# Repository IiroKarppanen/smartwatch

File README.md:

## Features
- nRF5340 SoC
- 240x240 LCD display
- Pulseoximetry
- GNSS
- Accelometer & Gyroscope
- Accurate RTC with backup battery

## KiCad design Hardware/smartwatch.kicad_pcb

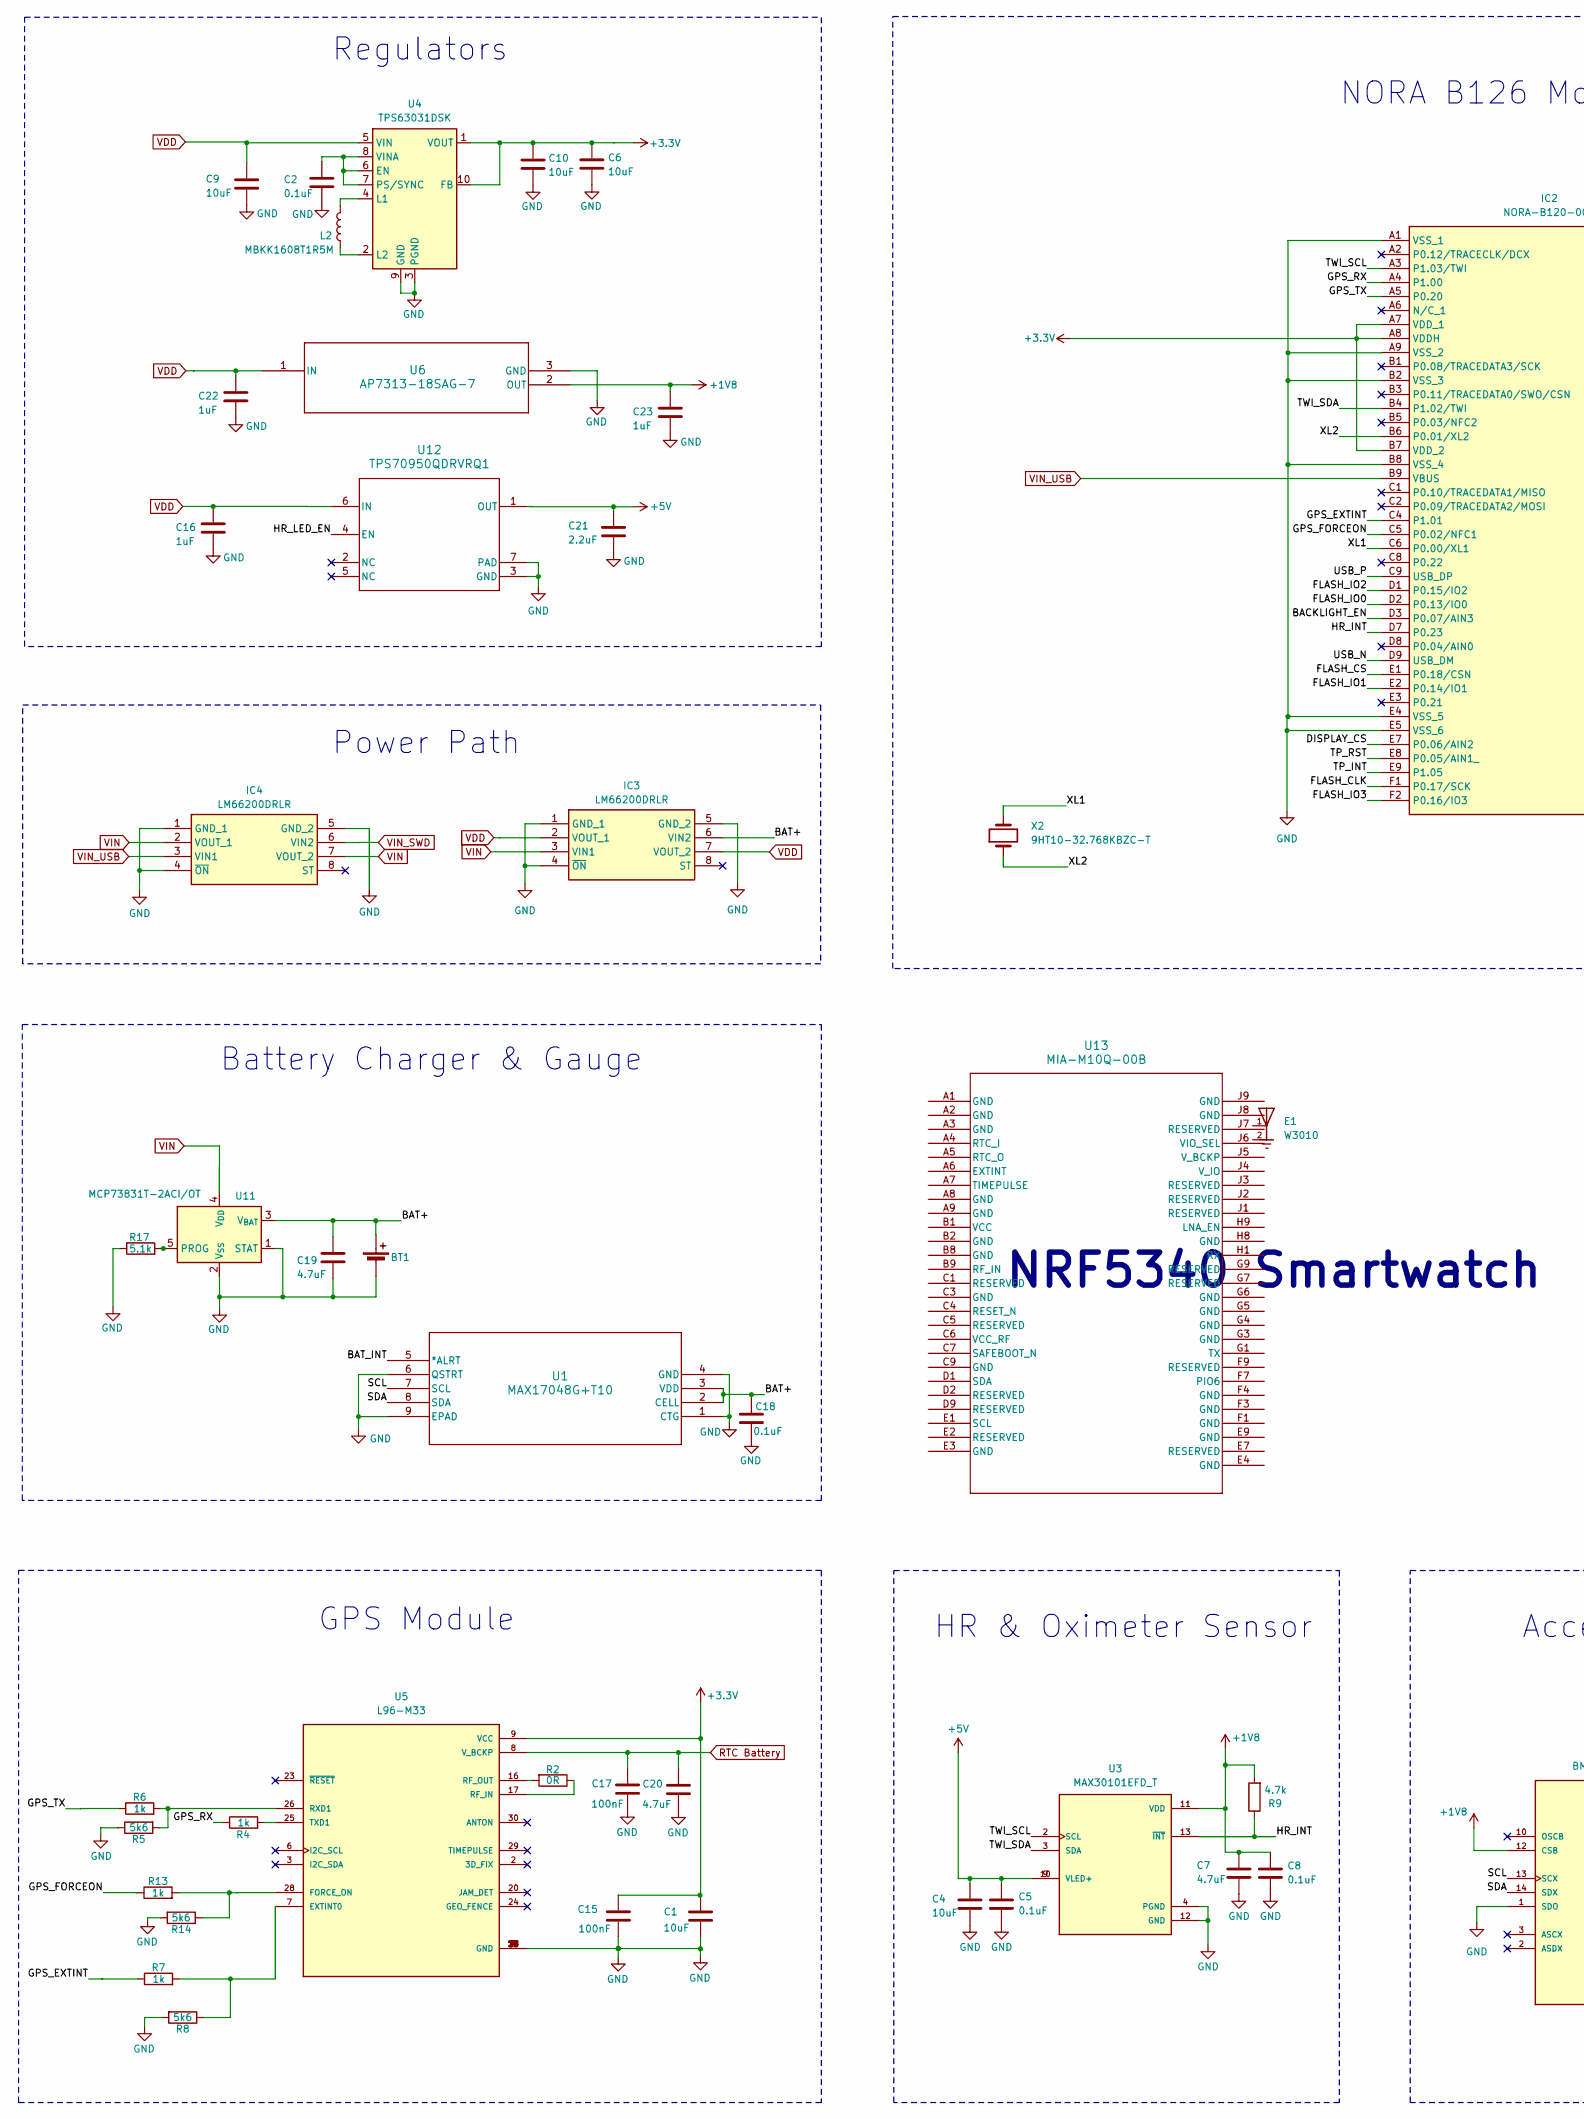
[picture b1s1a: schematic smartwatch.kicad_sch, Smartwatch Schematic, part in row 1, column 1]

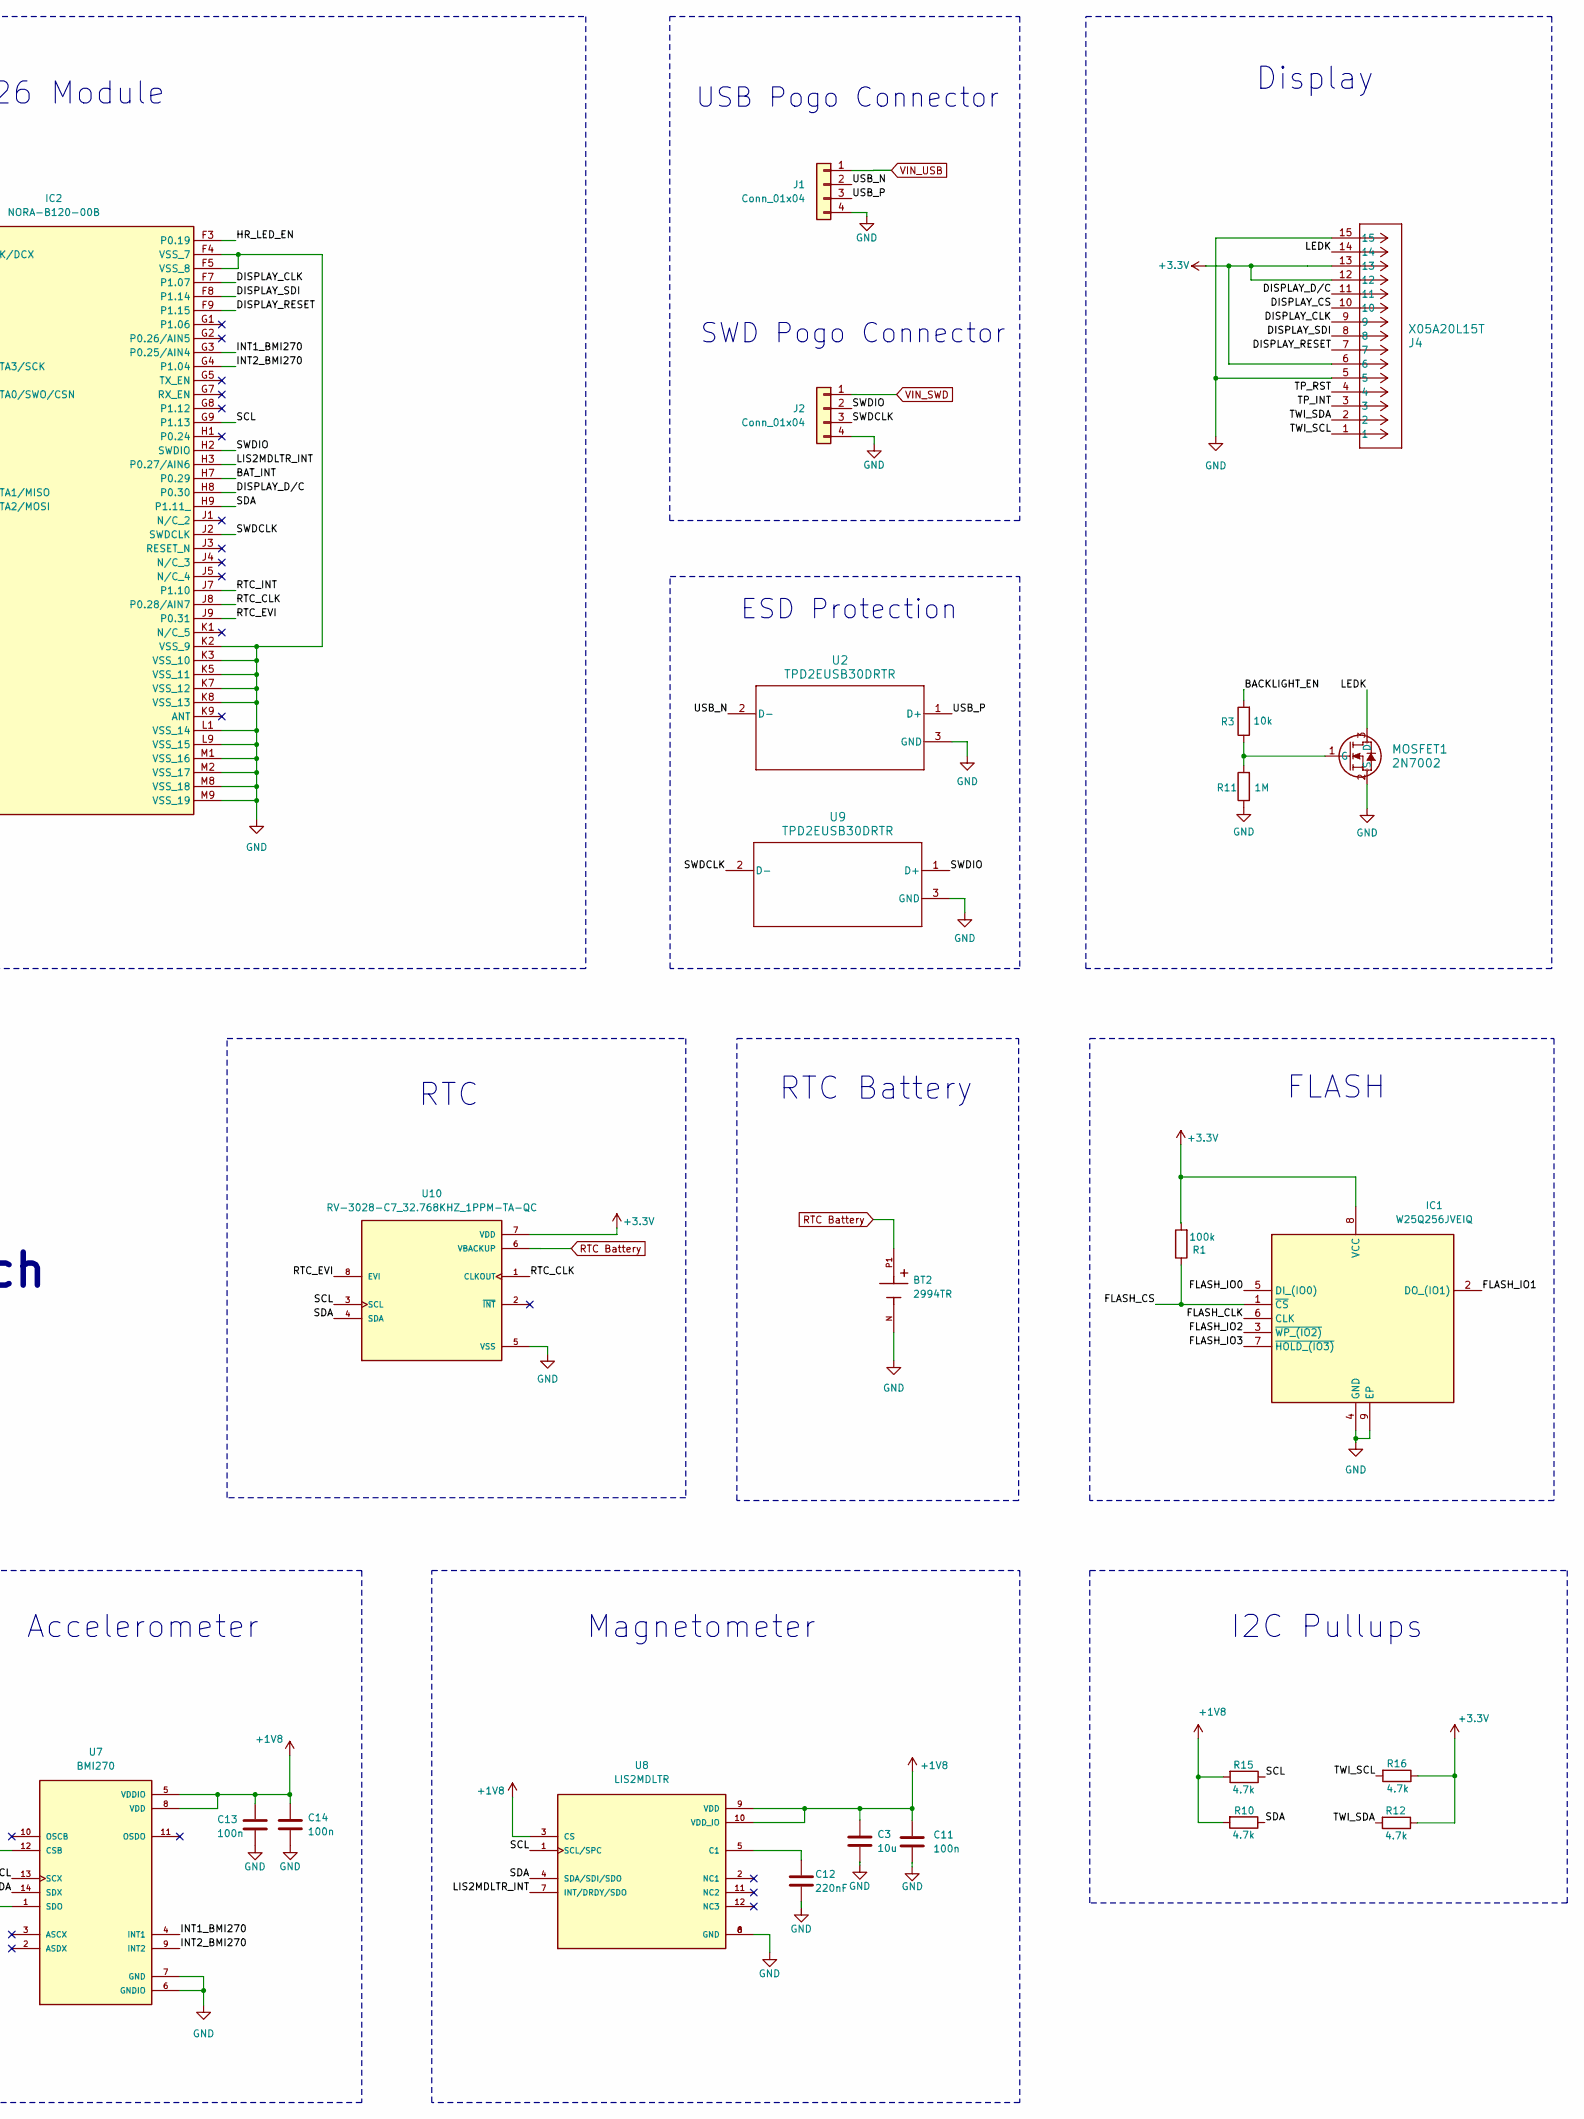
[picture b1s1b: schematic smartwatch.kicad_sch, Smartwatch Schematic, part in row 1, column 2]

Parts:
BT1: Battery_Cell; C_1812_4532Metric_Pad1.57x3.40mm_HandSolder
BT2: 2994TR; BAT_2994TR; PARTREV E
C1, C4, C6, C9, C10: 10uF; C_0402_1005Metric
C2, C5, C8: 0.1uF; C_0402_1005Metric
C3: 10u; C_0201_0603Metric
C7, C19, C20: 4.7uF; C_0402_1005Metric
C11, C13, C14: 100n; C_0201_0603Metric
C12: 220nF; C_0201_0603Metric
C15, C17: 100nF; C_0402_1005Metric
C16, C22, C23: 1uF; C_0402_1005Metric
C18: 0.1uF; C_0201_0603Metric
C21: 2.2uF; C_0402_1005Metric
E1: W3010; XCVR_W3010; PARTREV L192.C 2/16
IC1: W25Q256JVEIQ; SON127P800X600X80-9N-D; Mouser Part Number 454-W25N01GVZEIGTR
IC2: NORA-B120-00B; NORAB12000B; Mouser Part Number 377-NORA-B120-00B
IC3, IC4: LM66200DRLR; SOTFL50P160X60-8N; Mouser Part Number 595-LM66200DRLR
J1, J2: Conn_01x04; Pogo_Female_4Pin
J4: X05A20L15T; CONN_X05A20L15T_XKB
L2: MBKK1608T1R5M; L_0603_1608Metric
MOSFET1: 2N7002; SOT-23TO-236_318-08_ONS
R1: 100k; R_0402_1005Metric; MPN NRF52840-QIAA-R
R2: 0R; R_0402_1005Metric
R3: 10k; R_0402_1005Metric
R4, R6, R7, R13: 1k; R_0402_1005Metric
R5, R8, R14: 5k6; R_0402_1005Metric
R9: 4.7k; R_0402_1005Metric; MPN NRF52840-QIAA-R
R10, R12, R15, R16: 4.7k; R_0201_0603Metric; MPN NRF52840-QIAA-R
R11: 1M; R_0402_1005Metric
R17: 5.1k; R_0402_1005Metric
U1: MAX17048G+T10; 21-0168E_T822-3_MXM
U2, U9: TPD2EUSB30DRTR; DRT0003A
U3: MAX30101EFD_T; PARTREV 2
U4: TPS63031DSK; WSON-10-1EP_2.5x2.5mm_P0.5mm_EP1.2x2mm
U5: L96-M33; XCVR_L96-M33; DigiKey_Part_Number 2958-L96-M33TR-ND
U6: AP7313-18SAG-7; SOT-23_DIO
U7: BMI270; XDCR_BMI270
U8: LIS2MDLTR; PQFN50P200X200X70-12N; PARTREV Rev 5
U10: RV-3028-C7_32.768KHZ_1PPM-TA-QC; IC_RV-3028-C7_32.768KHZ_1PPM-TA-QC; PARTREV 1.3
U11: MCP73831T-2ACI/OT; SOT-23-5; MPN MCP73831-2-OT
U12: TPS70950QDRVRQ1; DRV0006A
U13: MIA-M10Q-00B; LGA_M10Q-00B_UBL
X2: 9HT10-32.768KBZC-T; Crystal_SMD_3215-2Pin_3.2x1.5mm

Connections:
+1V8: C3.1, C7.1, C8.1, C11.1, C13.1, C14.1, C23.1, R9.2, R10.2, R15.2, U3.11 (VDD), U6.2 (OUT), U7.5 (VDDIO), U7.8 (VDD), U7.12 (CSB), U8.3 (CS), U8.9 (VDD), U8.10 (VDD_IO)
+3.3V: C1.1, C6.1, C10.1, C15.1, IC1.8 (VCC), IC2.A7 (VDD_1), IC2.A8 (VDDH), IC2.B7 (VDD_2), J4.6, J4.12, J4.13, R1.2, R12.1, R16.1, U4.1 (VOUT), U4.10 (FB), U5.9 (VCC), U10.7 (VDD)
+5V: C4.1, C5.1, C21.1, U3.9 (VLED+), U3.10 (VLED+), U12.1 (OUT)
/BACKLIGHT_EN: IC2.D3 (P0.07/AIN3), R3.2
/BAT+: BT1.1 (+), C18.1, C19.1, IC3.6 (VIN2), U1.2 (CELL), U1.3 (VDD), U11.3 (V_{BAT})
/BAT_INT: IC2.H7 (P0.29), U1.5 (*ALRT)
/DISPLAY_CLK: IC2.F7 (P1.07), J4.9
/DISPLAY_CS: IC2.E7 (P0.06/AIN2), J4.10
/DISPLAY_D/C: IC2.H8 (P0.30), J4.11
/DISPLAY_RESET: IC2.F9 (P1.15), J4.7
/DISPLAY_SDI: IC2.F8 (P1.14), J4.8
/FLASH_CLK: IC1.6 (CLK), IC2.F1 (P0.17/SCK)
/FLASH_CS: IC1.1 (~CS), IC2.E1 (P0.18/CSN), R1.1
/FLASH_IO0: IC1.5 (DI_(IO0)), IC2.D2 (P0.13/IO0)
/FLASH_IO1: IC1.2 (DO_(IO1)), IC2.E2 (P0.14/IO1)
/FLASH_IO2: IC1.3 (~WP_(IO2)), IC2.D1 (P0.15/IO2)
/FLASH_IO3: IC1.7 (~HOLD_(IO3)), IC2.F2 (P0.16/IO3)
/GPS_EXTINT: IC2.C4 (P1.01), R7.1
/GPS_FORCEON: IC2.C5 (P0.02/NFC1), R13.1
/GPS_RX: IC2.A4 (P1.00), R4.1
/GPS_TX: IC2.A5 (P0.20), R6.1
/HR_INT: IC2.D7 (P0.23), R9.1, U3.13 (~INT)
/HR_LED_EN: IC2.F3 (P0.19), U12.4 (EN)
/INT1_BMI270: IC2.G3 (P0.25/AIN4), U7.4 (INT1)
/INT2_BMI270: IC2.G4 (P1.04), U7.9 (INT2)
/LEDK: J4.14, MOSFET1.3 (D)
/LIS2MDLTR_INT: IC2.H3 (P0.27/AIN6), U8.7 (INT/DRDY/SDO)
/RTC_CLK: IC2.J8 (P0.28/AIN7), U10.1 (CLKOUT)
/RTC_EVI: IC2.J9 (P0.31), U10.8 (EVI)
/RTC_INT: IC2.J7 (P1.10)
/SCL: IC2.G9 (P1.13), R15.1, U1.7 (SCL), U7.13 (SCX), U8.1 (SCL/SPC), U10.3 (SCL)
/SDA: IC2.H9 (P1.11_), R10.1, U1.8 (SDA), U7.14 (SDX), U8.4 (SDA/SDI/SDO), U10.4 (SDA)
/SWDCLK: IC2.J2 (SWDCLK), J2.3, U9.2 (D-)
/SWDIO: IC2.H2 (SWDIO), J2.2, U9.1 (D+)
/TP_INT: IC2.E9 (P1.05), J4.3
/TP_RST: IC2.E8 (P0.05/AIN1_), J4.4
/TWI_SCL: IC2.A3 (P1.03/TWI), J4.1, R16.2, U3.2 (SCL)
/TWI_SDA: IC2.B4 (P1.02/TWI), J4.2, R12.2, U3.3 (SDA)
/USB_N: IC2.D9 (USB_DM), J1.2, U2.2 (D-)
/USB_P: IC2.C9 (USB_DP), J1.3, U2.1 (D+)
/XL1: IC2.C6 (P0.00/XL1), X2.2
/XL2: IC2.B6 (P0.01/XL2), X2.1
GND: BT1.2 (-), BT2.N, C1.2, C2.2, C3.2, C4.2, C5.2, C6.2, C7.2, C8.2, C9.2, C10.2, C11.2, C12.2, C13.2, C14.2, C15.2, C16.2, C17.2, C18.2, C19.2, C20.2, C21.2, C22.2, C23.2, IC1.4 (GND), IC1.9 (EP), IC2.A1 (VSS_1), IC2.A9 (VSS_2), IC2.B2 (VSS_3), IC2.B8 (VSS_4), IC2.E4 (VSS_5), IC2.E5 (VSS_6), IC2.F4 (VSS_7), IC2.F5 (VSS_8), IC2.K2 (VSS_9), IC2.K3 (VSS_10), IC2.K5 (VSS_11), IC2.K7 (VSS_12), IC2.K8 (VSS_13), IC2.L1 (VSS_14), IC2.L9 (VSS_15), IC2.M1 (VSS_16), IC2.M2 (VSS_17), IC2.M8 (VSS_18), IC2.M9 (VSS_19), IC3.1 (GND_1), IC3.4 (~ON), IC3.5 (GND_2), IC4.1 (GND_1), IC4.4 (~ON), IC4.5 (GND_2), J1.4, J2.4, J4.5, J4.15, MOSFET1.2 (S), R5.1, R8.2, R11.1, R14.2, R17.1, U1.1 (CTG), U1.4 (GND), U1.6 (QSTRT), U1.9 (EPAD), U2.3 (GND), U3.4 (PGND), U3.12 (GND), U4.3 (PGND), U4.9 (GND), U4.11 (PGND), U5.4 (GND), U5.5 (GND), U5.10 (GND), U5.11 (GND), U5.12 (GND), U5.13 (GND), U5.14 (GND), U5.15 (GND), U5.18 (GND), U5.19 (GND), U5.21 (GND), U5.22 (GND), U5.27 (GND), U5.31 (GND), U6.3 (GND), U7.1 (SDO), U7.6 (GNDIO), U7.7 (GND), U8.6 (GND), U8.8 (GND), U9.3 (GND), U10.5 (VSS), U11.1 (STAT), U11.2 (V_{SS}), U12.3 (GND), U12.7 (PAD)
unnamed: MOSFET1.1 (G), R3.1, R11.2
unnamed: C2.1, U4.6 (EN), U4.7 (PS/SYNC), U4.8 (VINA)
unnamed: L2.2, U4.4 (L1)
unnamed: L2.1, U4.2 (L2)
unnamed: R7.2, R8.1, U5.7 (EXTINT0)
unnamed: R13.2, R14.1, U5.28 (FORCE_ON)
unnamed: R2.1, U5.17 (RF_IN)
unnamed: R2.2, U5.16 (RF_OUT)
unnamed: R5.2, R6.2, U5.26 (RXD1)
unnamed: R4.2, U5.25 (TXD1)
unnamed: C12.1, U8.5 (C1)
unnamed: R17.2, U11.5 (PROG)
RTC Battery: BT2.P1, C17.1, C20.1, U5.8 (V_BCKP), U10.6 (VBACKUP)
VDD: C9.1, C16.1, C22.1, IC3.2 (VOUT_1), IC3.7 (VOUT_2), U4.5 (VIN), U6.1 (IN), U12.6 (IN)
VIN: IC3.3 (VIN1), IC4.2 (VOUT_1), IC4.7 (VOUT_2), U11.4 (V_{DD})
VIN_SWD: IC4.6 (VIN2), J2.1
VIN_USB: IC2.B9 (VBUS), IC4.3 (VIN1), J1.1

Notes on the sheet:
NORA B126 Module
NRF5340 Smartwatch
HR & Oximeter Sensor
Magnetometer
GPS Module
I2C Pullups
SWD Pogo Connector
RTC Battery
Battery Charger & Gauge
Display
Accelerometer
USB Pogo Connector
ESD Protection
FLASH
Power Path
RTC
Regulators

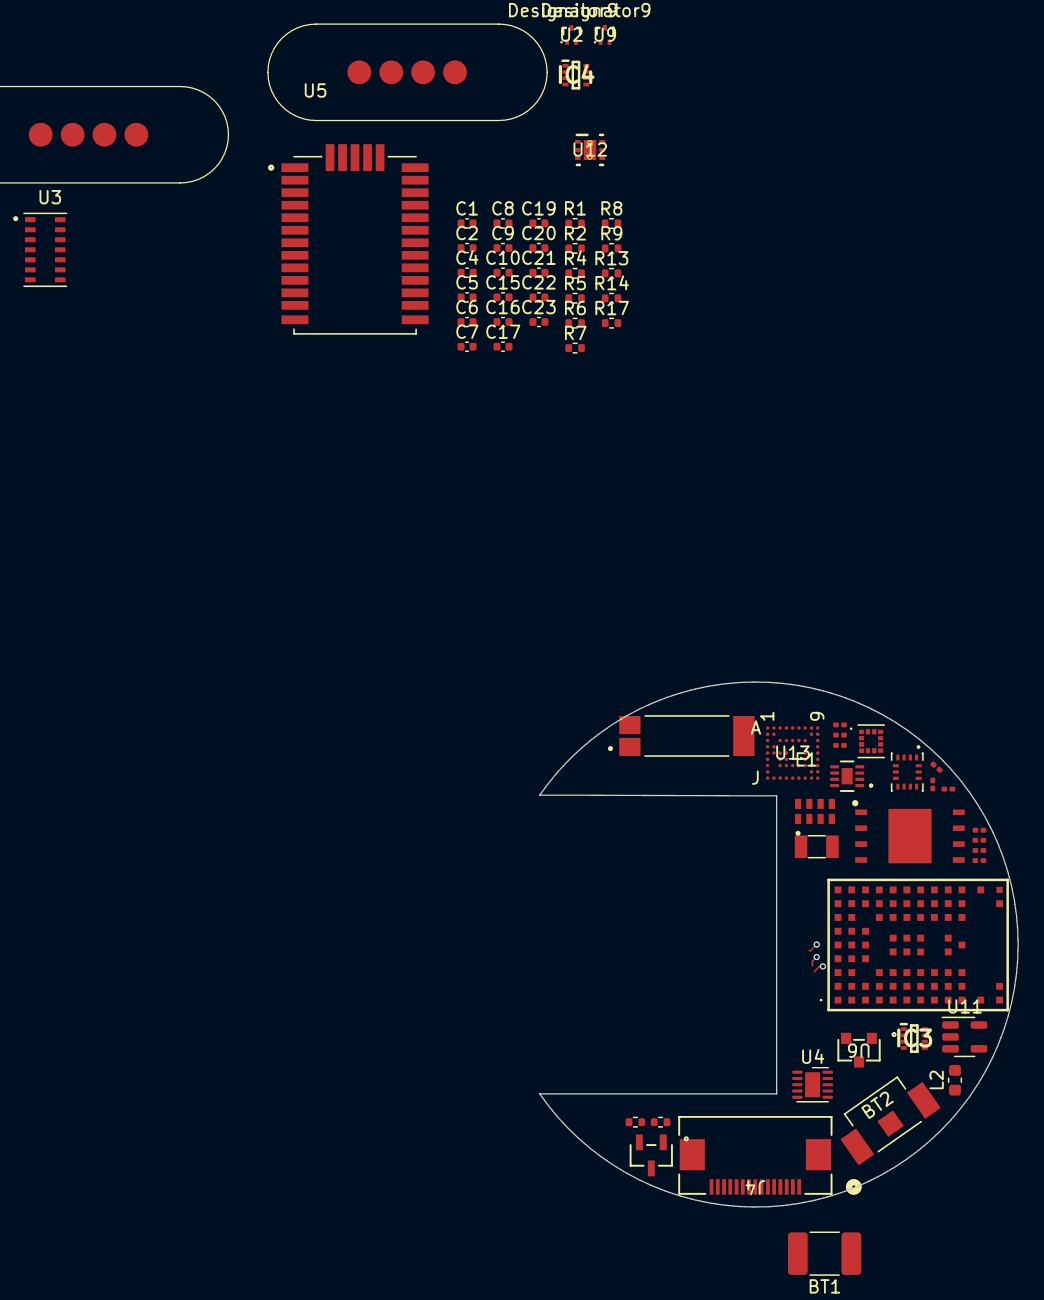
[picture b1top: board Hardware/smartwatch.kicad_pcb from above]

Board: 4 copper layers, 38.2 x 41.9 mm, 66 parts (0 on the bottom side), 59 nets.

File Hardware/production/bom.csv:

Designator,Footprint,Quantity,Value,LCSC Part #
BT1,1812,1,Battery_Cell,
BT2,BAT_2994TR,1,2994TR,
"C1, C10, C4, C6, C9",0402,5,10uF,
"C11, C13, C14",0402,3,100n,
C12,0402,1,220nF,
"C15, C17",0402,2,100nF,
"C16, C22, C23",0402,3,1uF,
"C18, C2, C5, C8",0402,4,0.1uF,
"C19, C20, C7",0402,3,4.7uF,
C21,0402,1,2.2uF,
C3,0402,1,10u,
IC1,SON127P800X600X80-9N-D,1,W25Q256JVEIQ,
IC2,NORAB12000B,1,NORA-B120-00B,
"IC3, IC4",SOTFL50P160X60-8N,2,LM66200DRLR,
"J1, J2",Pogo_Female_4Pin,2,Conn_01x04,
J4,CONN_X05A20L15T_XKB,1,X05A20L15T,
L2,0603,1,MBKK1608T1R5M,
MOSFET1,SOT-23TO-236_318-08_ONS,1,2N7002,
R1,0402,1,100k,NRF52840-QIAA-R
"R10, R12, R15, R16, R9",0402,5,4.7k,NRF52840-QIAA-R
R11,0402,1,1M,
"R13, R4, R6, R7",0402,4,1k,
"R14, R5, R8",0402,3,5k6,
R17,0402,1,5.1k,
R18,0805,1,470,
R2,0402,1,0R,
R3,0402,1,10k,
U1,21-0168E_T822-3_MXM,1,MAX17048G+T10,
U10,IC_RV-3028-C7_32.768KHZ_1PPM-TA-QC,1,RV-3028-C7_32.768KHZ_1PPM-TA-QC,
U11,SOT-23-5,1,MCP73831T-2ACI/OT,MCP73831-2-OT
U12,DRV0006A,1,TPS70950QDRVRQ1,
"U2, U9",DRT0003A,2,TPD2EUSB30DRTR,
U3,MAX30101EFD_T,1,MAX30101EFD_T,
U4,WSON-10-1EP_2.5x2.5mm_P0.5mm_EP1.2x2mm,1,TPS63031DSK,
U5,XCVR_L96-M33,1,L96-M33,
U6,SOT-23_DIO,1,AP7313-18SAG-7,
U7,XDCR_BMI270,1,BMI270,
U8,PQFN50P200X200X70-12N,1,LIS2MDLTR,
X2,Crystal_SMD_3215-2Pin_3.2x1.5mm,1,9HT10-32.768KBZC-T,

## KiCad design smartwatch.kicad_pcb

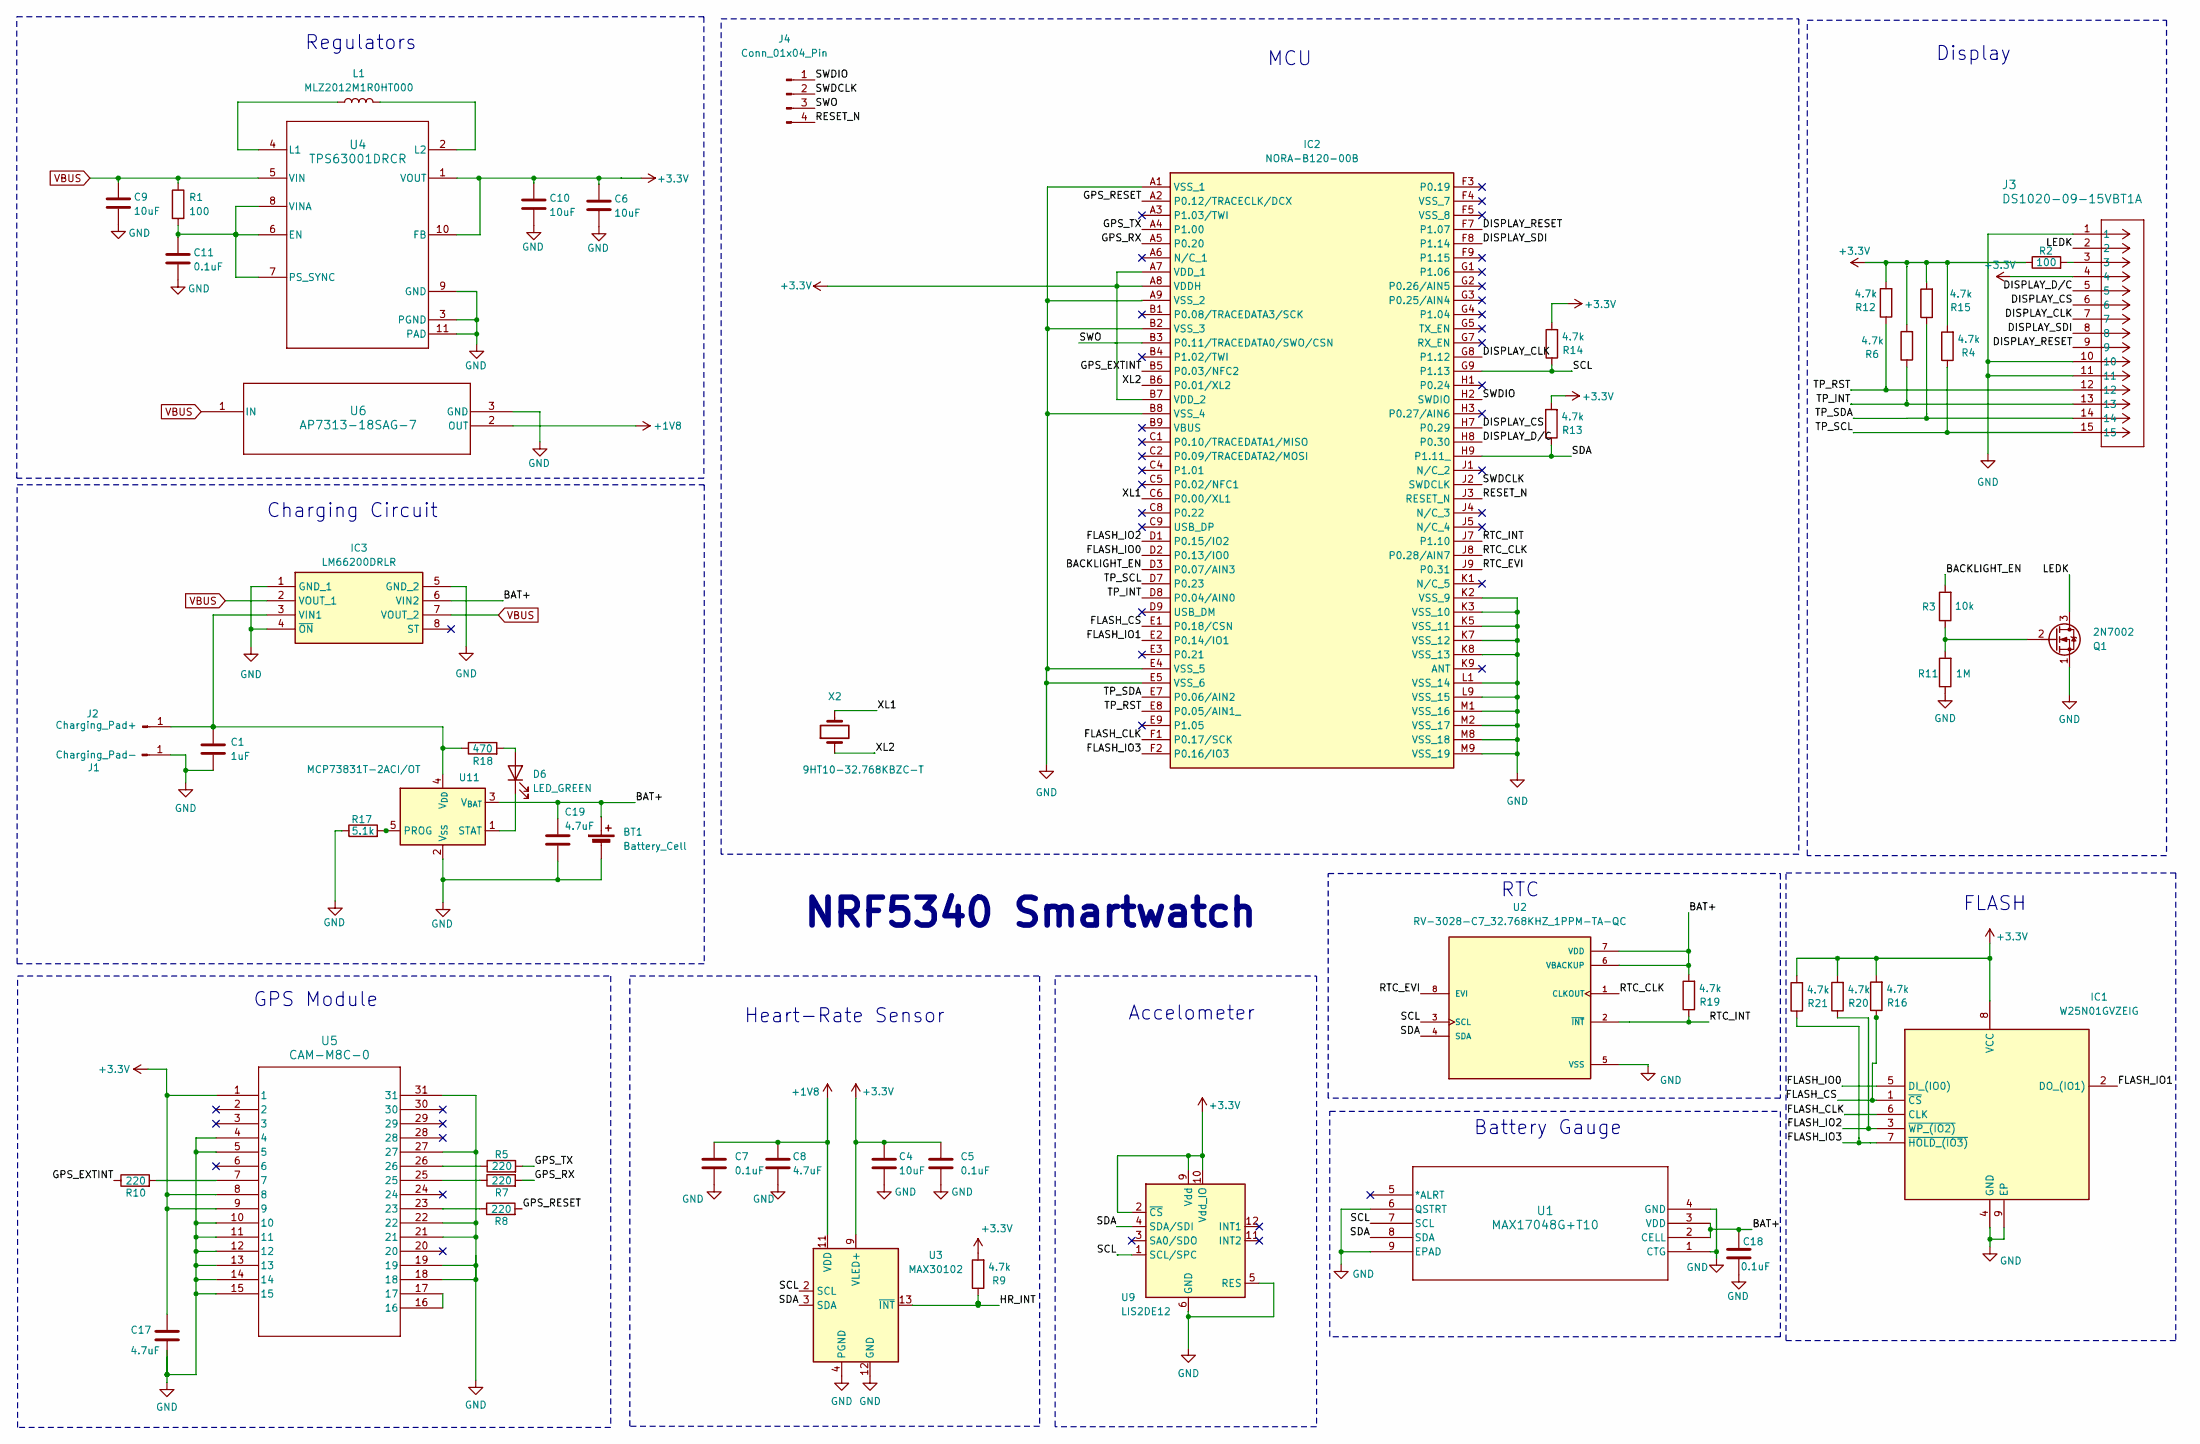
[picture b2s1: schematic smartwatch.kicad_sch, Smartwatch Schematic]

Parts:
BT1: Battery_Cell; C_1812_4532Metric
C1: 1uF; C_0402_1005Metric
C4, C6, C9, C10: 10uF; C_0402_1005Metric
C5, C7, C11, C18: 0.1uF; C_0402_1005Metric
C8, C17, C19: 4.7uF; C_0402_1005Metric
D6: LED_GREEN; LED_0402_1005Metric
IC1: W25N01GVZEIG; SON127P800X600X80-9N-D; Mouser Part Number 454-W25N01GVZEIGTR
IC2: NORA-B120-00B; NORAB12000B; Mouser Part Number 377-NORA-B120-00B
IC3: LM66200DRLR; SOTFL50P160X60-8N; Mouser Part Number 595-LM66200DRLR
J1: Charging_Pad-; power_pad_4mm
J2: Charging_Pad+; power_pad_4mm
J3: DS1020-09-15VBT1A; FPC-SMD_P0.50-15P_LSXJ-H2.0-15P
J4: Conn_01x04_Pin; PinHeader_1x04_P2.54mm_Vertical
L1: MLZ2012M1R0HT000; L_0805_2012Metric
Q1: 2N7002; SOT-23-3
R1: 100; R_0402_1005Metric
R2: 100; R_0603_1608Metric
R3: 10k; R_0603_1608Metric
R4, R6, R9, R12, R15, R16, R19, R20, R21: 4.7k; R_0402_1005Metric; MPN NRF52840-QIAA-R
R5, R7, R8, R10: 220; R_0402_1005Metric
R11: 1M; R_0603_1608Metric
R13, R14: 4.7k; R_0603_1608Metric; MPN NRF52840-QIAA-R
R17: 5.1k; R_0402_1005Metric
R18: 470; R_0402_1005Metric
U1: MAX17048G+T10; 21-0168E_T822-3_MXM
U2: RV-3028-C7_32.768KHZ_1PPM-TA-QC; IC_RV-3028-C7_32.768KHZ_1PPM-TA-QC; PARTREV 1.3
U3: MAX30102; Maxim_OLGA-14_3.3x5.6mm_P0.8mm
U4: TPS63001DRCR; DRC0010J
U5: CAM-M8C-0; QFN_M8C-0_UBL
U6: AP7313-18SAG-7; SOT-23_DIO
U9: LIS2DE12; LGA-12_2x2mm_P0.5mm; MPN LIS2DE12
U11: MCP73831T-2ACI/OT; SOT-23-5; MPN MCP73831-2-OT
X2: 9HT10-32.768KBZC-T; Crystal_SMD_3215-2Pin_3.2x1.5mm

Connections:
+1V8: C7.1, C8.1, U3.11 (VDD), U6.2 (OUT)
+3.3V: C4.1, C5.1, C6.1, C10.1, C17.1, IC1.8 (VCC), IC2.A7 (VDD_1), IC2.A8 (VDDH), IC2.B7 (VDD_2), J3.4, R2.1, R4.2, R6.2, R9.2, R12.2, R13.2, R14.2, R15.2, R16.2, R20.2, R21.2, U3.9 (VLED+), U3.10 (VLED+), U4.1 (VOUT), U4.10 (FB), U5.1, U5.8, U5.9, U9.2 (~CS), U9.9 (Vdd), U9.10 (Vdd_IO)
/BACKLIGHT_EN: IC2.D3 (P0.07/AIN3), R3.2
/BAT+: BT1.1 (+), C18.1, C19.1, IC3.6 (VIN2), R19.2, U1.2 (CELL), U1.3 (VDD), U2.6 (VBACKUP), U2.7 (VDD), U11.3 (V_{BAT})
/DISPLAY_CLK: IC2.G8 (P1.12), J3.7
/DISPLAY_CS: IC2.H7 (P0.29), J3.6
/DISPLAY_D/C: IC2.H8 (P0.30), J3.5
/DISPLAY_RESET: IC2.F7 (P1.07), J3.9
/DISPLAY_SDI: IC2.F8 (P1.14), J3.8
/FLASH_CLK: IC1.6 (CLK), IC2.F1 (P0.17/SCK)
/FLASH_CS: IC1.1 (~CS), IC2.E1 (P0.18/CSN), R16.1
/FLASH_IO0: IC1.5 (DI_(IO0)), IC2.D2 (P0.13/IO0)
/FLASH_IO1: IC1.2 (DO_(IO1)), IC2.E2 (P0.14/IO1)
/FLASH_IO2: IC1.3 (~WP_(IO2)), IC2.D1 (P0.15/IO2), R20.1
/FLASH_IO3: IC1.7 (~HOLD_(IO3)), IC2.F2 (P0.16/IO3), R21.1
/GPS_EXTINT: IC2.B5 (P0.03/NFC2), R10.1
/GPS_RESET: IC2.A2 (P0.12/TRACECLK/DCX), R8.2
/GPS_RX: IC2.A5 (P0.20), R7.2
/GPS_TX: IC2.A4 (P1.00), R5.2
/HR_INT: R9.1, U3.13 (~INT)
/LEDK: J3.2, Q1.3 (D)
/RESET_N: IC2.J3 (RESET_N), J4.4
/RTC_CLK: IC2.J8 (P0.28/AIN7), U2.1 (CLKOUT)
/RTC_EVI: IC2.J9 (P0.31), U2.8 (EVI)
/RTC_INT: IC2.J7 (P1.10), R19.1, U2.2 (~INT)
/SCL: IC2.G9 (P1.13), R14.1, U1.7 (SCL), U2.3 (SCL), U3.2 (SCL), U9.1 (SCL/SPC)
/SDA: IC2.H9 (P1.11_), R13.1, U1.8 (SDA), U2.4 (SDA), U3.3 (SDA), U9.4 (SDA/SDI)
/SWDCLK: IC2.J2 (SWDCLK), J4.2
/SWDIO: IC2.H2 (SWDIO), J4.1
/SWO: IC2.B3 (P0.11/TRACEDATA0/SWO/CSN), J4.3
/TP_INT: IC2.D8 (P0.04/AIN0), J3.13, R6.1
/TP_RST: IC2.E8 (P0.05/AIN1_), J3.12, R12.1
/TP_SCL: IC2.D7 (P0.23), J3.15, R4.1
/TP_SDA: IC2.E7 (P0.06/AIN2), J3.14, R15.1
/XL1: IC2.C6 (P0.00/XL1), X2.2
/XL2: IC2.B6 (P0.01/XL2), X2.1
GND: BT1.2 (-), C1.2, C4.2, C5.2, C6.2, C7.2, C8.2, C9.2, C10.2, C11.2, C17.2, C18.2, C19.2, IC1.4 (GND), IC1.9 (EP), IC2.A1 (VSS_1), IC2.A9 (VSS_2), IC2.B2 (VSS_3), IC2.B8 (VSS_4), IC2.E4 (VSS_5), IC2.E5 (VSS_6), IC2.K2 (VSS_9), IC2.K3 (VSS_10), IC2.K5 (VSS_11), IC2.K7 (VSS_12), IC2.K8 (VSS_13), IC2.L1 (VSS_14), IC2.L9 (VSS_15), IC2.M1 (VSS_16), IC2.M2 (VSS_17), IC2.M8 (VSS_18), IC2.M9 (VSS_19), IC3.1 (GND_1), IC3.4 (~ON), IC3.5 (GND_2), J1.1, J3.1, J3.10, J3.11, Q1.1 (S), R11.1, R17.1, U1.1 (CTG), U1.4 (GND), U1.6 (QSTRT), U1.9 (EPAD), U2.5 (VSS), U3.4 (PGND), U3.12 (GND), U4.3 (PGND), U4.9 (GND), U4.11 (PAD), U4.V, U5.4, U5.5, U5.10, U5.11, U5.12, U5.13, U5.14, U5.15, U5.18, U5.19, U5.21, U5.22, U5.27, U5.31, U6.3 (GND), U9.5 (RES), U9.6 (GND), U9.7 (GND), U9.8 (GND), U11.2 (V_{SS})
unnamed: D6.2 (A), R18.2
unnamed: D6.1 (K), U11.1 (STAT)
unnamed: C1.1, IC3.3 (VIN1), J2.1, R18.1, U11.4 (V_{DD})
unnamed: J3.3, R2.2
unnamed: Q1.2 (G), R3.1, R11.2
unnamed: R5.1, U5.26
unnamed: R7.1, U5.25
unnamed: R8.1, U5.23
unnamed: R10.2, U5.7
unnamed: C11.1, R1.2, U4.6 (EN), U4.7 (PS_SYNC), U4.8 (VINA)
unnamed: L1.1, U4.4 (L1)
unnamed: L1.2, U4.2 (L2)
unnamed: U5.16, U5.17
unnamed: R17.2, U11.5 (PROG)
VBUS: C9.1, IC3.2 (VOUT_1), IC3.7 (VOUT_2), R1.1, U4.5 (VIN), U6.1 (IN)

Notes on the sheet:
MCU
NRF5340 Smartwatch
RTC
Accelometer
Heart-Rate Sensor
Battery Gauge
Display
FLASH
Charging Circuit
GPS Module
Regulators

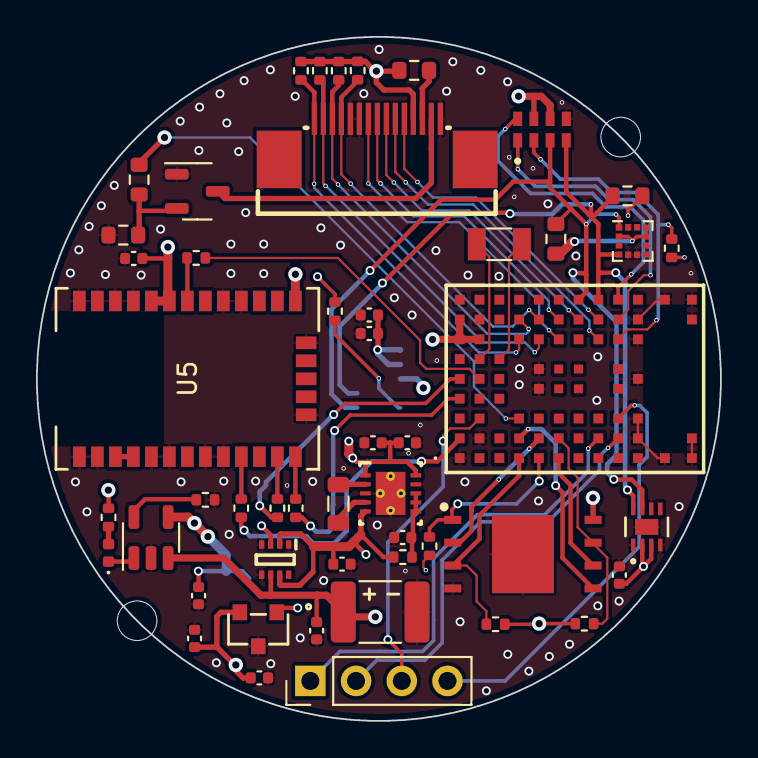
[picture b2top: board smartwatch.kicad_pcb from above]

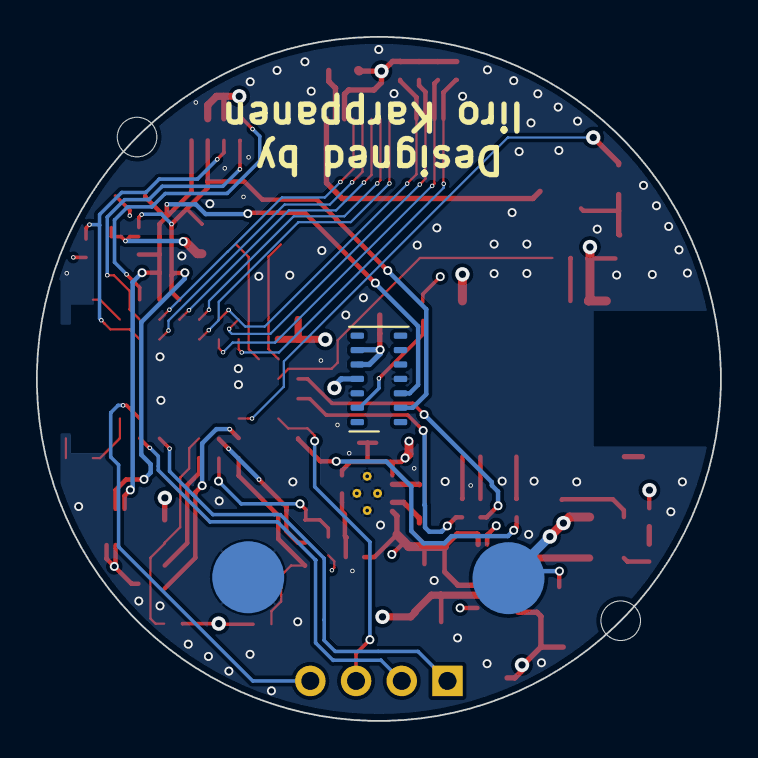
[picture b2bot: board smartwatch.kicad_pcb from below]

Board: 4 copper layers, 38.0 x 38.0 mm, 53 parts (3 on the bottom side), 52 nets.

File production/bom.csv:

Designator,Footprint,Quantity,Value,LCSC Part #
BT1,1812,1,Battery_Cell,
C1,0402,1,1uF,
"C10, C4, C6, C9",0402,4,10uF,
"C11, C18, C5, C7",0402,4,0.1uF,
"C17, C19, C8",0402,3,4.7uF,
D6,0402,1,LED_GREEN,
IC1,SON127P800X600X80-9N-D,1,W25N01GVZEIG,
IC2,NORAB12000B,1,NORA-B120-00B,
IC3,SOTFL50P160X60-8N,1,LM66200DRLR,
J1,power_pad_4mm,1,Charging_Pad-,
J2,power_pad_4mm,1,Charging_Pad+,
J3,FPC-SMD_P0.50-15P_LSXJ-H2.0-15P,1,DS1020-09-15VBT1A,
J4,PinHeader_1x04_P2.54mm_Vertical,1,Conn_01x04_Pin,
L1,0805,1,MLZ2012M1R0HT000,
Q1,SOT-23-3,1,2N7002,
R1,0402,1,100,
"R10, R5, R7, R8",0402,4,220,
R11,0603,1,1M,
"R12, R15, R16, R19, R20, R21, R4, R6, R9",0402,9,4.7k,NRF52840-QIAA-R
"R13, R14",0603,2,4.7k,NRF52840-QIAA-R
R17,0402,1,5.1k,
R18,0402,1,470,
R2,0603,1,100,
R3,0603,1,10k,
U1,21-0168E_T822-3_MXM,1,MAX17048G+T10,
U11,SOT-23-5,1,MCP73831T-2ACI/OT,MCP73831-2-OT
U2,IC_RV-3028-C7_32.768KHZ_1PPM-TA-QC,1,RV-3028-C7_32.768KHZ_1PPM-TA-QC,
U3,Maxim_OLGA-14_3.3x5.6mm_P0.8mm,1,MAX30102,
U4,DRC0010J,1,TPS63001DRCR,
U5,QFN_M8C-0_UBL,1,CAM-M8C-0,
U6,SOT-23_DIO,1,AP7313-18SAG-7,
U9,LGA-12_2x2mm_P0.5mm,1,LIS2DE12,LIS2DE12
X2,Crystal_SMD_3215-2Pin_3.2x1.5mm,1,9HT10-32.768KBZC-T,

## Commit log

2023-10-04 pcb layout almost complete
2023-10-08 pcb complete
2023-10-28 changed gps module
2023-10-28 New rtc module
2023-10-31 changed to nrf5340 & did some rework to charging circuit
2023-11-03 added battery gauge
2023-11-03 charging circuit complete
2023-11-06 switched to 4 layers
2023-11-06 changed backlight resistor values
2023-11-06 worked on power traces & added mounting holes
2023-11-10 added lm66200
2023-11-13 signal routing 50% complete
2023-11-15 ready for production
2023-11-15 update 1
2023-12-25 v3 schema complete
2024-01-02 changed gps moduleto l96
2024-01-07 added rtc
2024-02-09 final version
2024-02-21 progress on display driver
2024-03-17 progress on UI
2024-04-07 added more ui elements
2024-04-18 implemented uart communication with gnss module
2024-04-22 first watchface complete
